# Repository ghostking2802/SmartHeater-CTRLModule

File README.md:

# Smart Heater Control Module 🔥

This project is a smart safety and control module for electric heaters. Designed using KiCad, it includes temperature monitoring, relay-based control, safety cutoffs, and visual feedback, all powered by a microcontroller (e.g., ESP32 or Arduino).

---

## 🧩 Features

- **Real-Time Temperature Monitoring**
- **Relay Control for Heater Switch**
- **Safety Cut-off with Thermal Fuse**
- **OLED Display for Status Info**
- **Manual Override Switch**
- **PCB Designed using KiCad**

---

## 📐 Block Diagram

---

## 🧪 Schematic

---

## 🛠️ PCB Layout Previews

---

## 📋 Bill of Materials (BOM)

| Component             | Qty | Cost     |
|-----------------------|-----|----------|
| ESP32 Dev Board       | 1   | Rs. 300  |
| DS18B20 Temp Sensor   | 1   | Rs. 100  |
| 5V Relay Module       | 1   | Rs. 60   |
| OLED Display (0.96")  | 1   | Rs. 150  |
| 7805 Regulator        | 1   | Rs. 15   |
| Discrete Components   | -   | Rs. 50   |
| PCB Fabrication       | 1   | Rs. 200  |

---

## 🔌 System Explanation

### Power Flow
AC Mains → Step-down SMPS → 5V/12V Regulated Supply → Microcontroller → Relay Control

### Sensor and Relay Logic
- If temperature < threshold → Relay ON → Heater ON  
- If temperature ≥ threshold → Relay OFF → Heater OFF  

### Safety & Fallback
- Thermal fuse as a hardware cutoff  
- Watchdog timer in software  
- Manual override and warning LED/OLED  

---

## 🧪 Test Plan

1. Simulate gradual temperature increase
2. Observe cutoff at 60°C
3. Check relay OFF and OLED warning
4. Allow manual reset below 50°C

---

## 📁 Project Structure

```
├── SmartHeaterControl.kicad_sch
├── SmartHeaterControl.kicad_pcb
├── gerber/
├── screenshots/
├── BlockDiagram.png
├── Schematic.png
└── PCB_View_*.png
```

---
## 💻 MCU Programming Guide

### Hardware Pin Mapping (ESP32)

| Component             | MCU Pin          |
|----------------------|------------------|
| DS18B20 Temp Sensor  | GPIO 4           |
| Relay Module (IN)    | GPIO 13          |
| OLED Display (I2C)   | SDA = GPIO 21, SCL = GPIO 22 |
| Buzzer / LED         | GPIO 14          |
| Manual Reset Button  | GPIO 12          |

> Note: DS18B20 needs a 4.7kΩ pull-up resistor on the data line.

---

### Required Libraries (Arduino IDE)

- `OneWire.h`
- `DallasTemperature.h`
- `Adafruit_GFX.h`
- `Adafruit_SSD1306.h`

---

### ESP32 Board Setup in Arduino IDE

1. Install board support:
   - Board Manager URL:  
     `https://raw.githubusercontent.com/espressif/arduino-esp32/gh-pages/package_esp32_index.json`
2. Select board: **ESP32 Dev Module**
3. Connect device via USB and select correct COM port
4. Install required libraries via Library Manager

---

## 👨‍💻 Author

**Soumabha Majumdar**  
📧 [soumabha.majumdar@gmail.com](mailto:soumabha.majumdar@gmail.com)  
📞 7003472159

---

## 📜 License

This project is open-source and free to use for academic and non-commercial purposes.

### 🔌 Sample Arduino Code

```cpp
#include <OneWire.h>
#include <DallasTemperature.h>
#include <Adafruit_GFX.h>
#include <Adafruit_SSD1306.h>

#define ONE_WIRE_BUS 4
#define RELAY_PIN 13
#define BUZZER_PIN 14
#define BUTTON_PIN 12

#define SCREEN_WIDTH 128
#define SCREEN_HEIGHT 64
Adafruit_SSD1306 display(SCREEN_WIDTH, SCREEN_HEIGHT, &Wire, -1);

OneWire oneWire(ONE_WIRE_BUS);
DallasTemperature sensors(&oneWire);

float cutoffTemp = 60.0;
float resumeTemp = 50.0;
bool manualReset = false;

void setup() {
  Serial.begin(115200);
  sensors.begin();

  pinMode(RELAY_PIN, OUTPUT);
  pinMode(BUZZER_PIN, OUTPUT);
  pinMode(BUTTON_PIN, INPUT_PULLUP);

  display.begin(SSD1306_SWITCHCAPVCC, 0x3C);
  display.clearDisplay();
  display.setTextSize(1);
  display.setTextColor(SSD1306_WHITE);
}

void loop() {
  sensors.requestTemperatures();
  float tempC = sensors.getTempCByIndex(0);

  display.clearDisplay();
  display.setCursor(0,0);
  display.print("Temp: ");
  display.print(tempC);
  display.print(" C");

  if (!manualReset && tempC < cutoffTemp) {
    digitalWrite(RELAY_PIN, HIGH);
    digitalWrite(BUZZER_PIN, LOW);
    display.setCursor(0,20);
    display.print("Status: Heater ON");
  } else if (!manualReset && tempC >= cutoffTemp) {
    digitalWrite(RELAY_PIN, LOW);
    digitalWrite(BUZZER_PIN, HIGH);
    display.setCursor(0,20);
    display.print("OVERHEAT! Relay OFF");
    display.setCursor(0,30);
    display.print("Press button to reset");
    manualReset = true;
  }

  if (manualReset && digitalRead(BUTTON_PIN) == LOW && tempC <= resumeTemp) {
    manualReset = false;
    digitalWrite(BUZZER_PIN, LOW);
  }

  display.display();
  delay(1000);
}

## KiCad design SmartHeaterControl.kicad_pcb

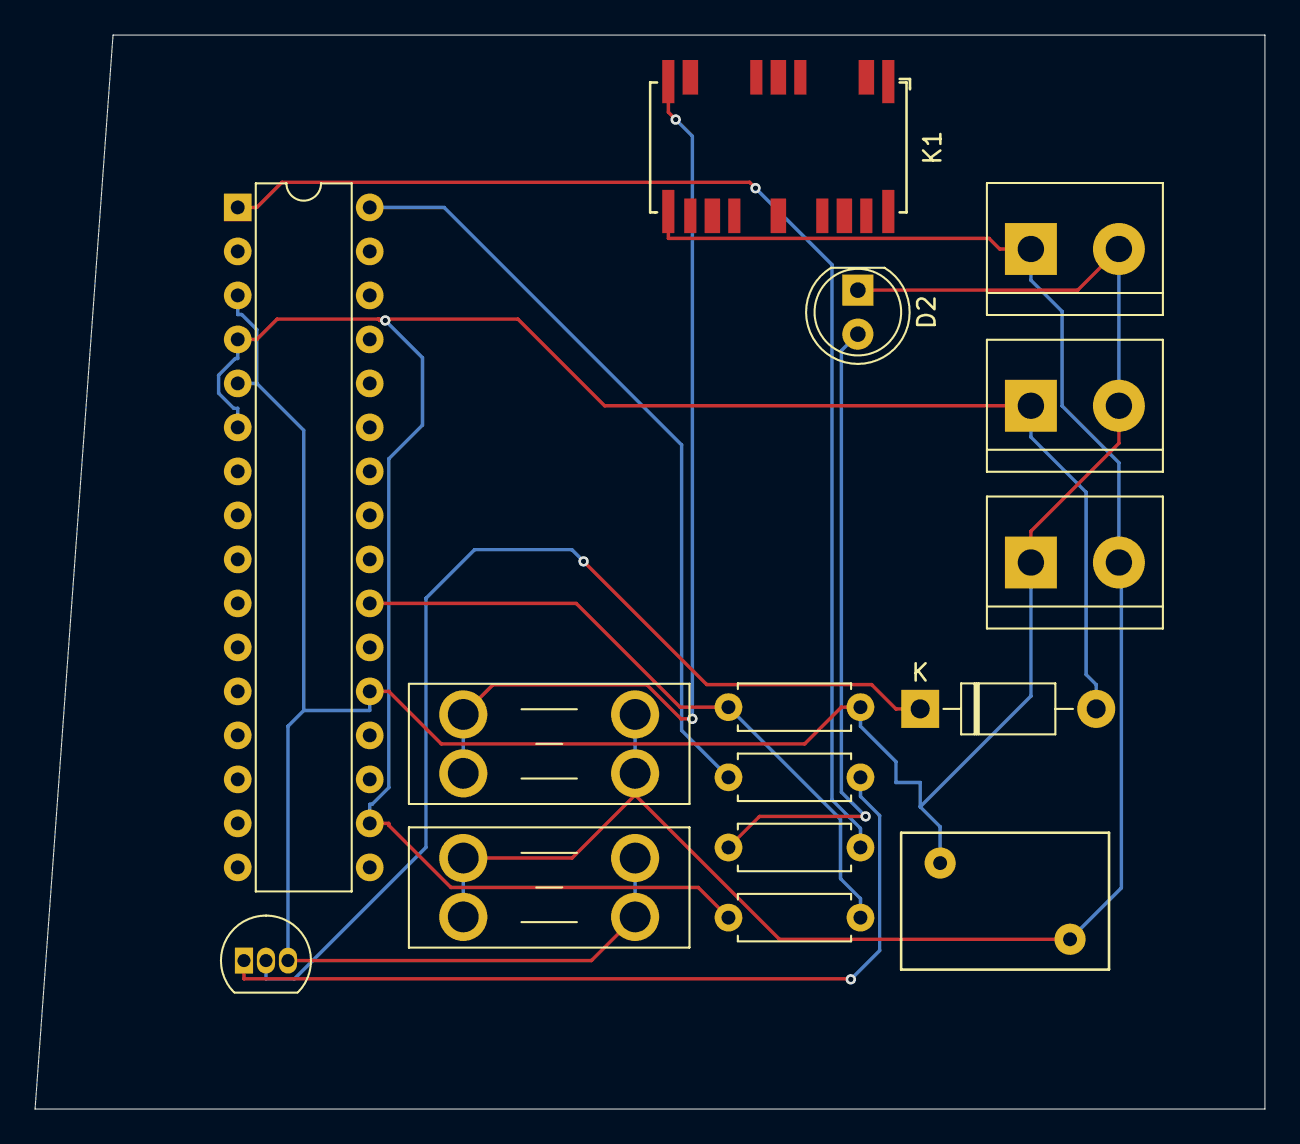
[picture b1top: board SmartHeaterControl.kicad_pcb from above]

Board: 2 copper layers, 71.0 x 62.0 mm, 15 parts (0 on the bottom side), 10 nets.

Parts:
D1: D; D_DO-41_SOD81_P10.16mm_Horizontal
D2: LED; LED_D5.0mm
F1, F2: Fuse; Fuseholder_Blade_Mini_Keystone_3568
J1, J2: Conn_01x02; TerminalBlock_bornier-2_P5.08mm
K1: Relay_SPDT; Relay_SPDT_AXICOM_HF3Series_50ohms_Pitch1.27mm
Q1: Q1; TO-92_Inline
R1, R2, R4: R; R_Axial_DIN0207_L6.3mm_D2.5mm_P7.62mm_Horizontal
R3: Heater; TerminalBlock_bornier-2_P5.08mm
RV1: Varistor; RV_Disc_D12mm_W7.9mm_P7.5mm
TH1: Thermistor_NTC; R_Axial_DIN0207_L6.3mm_D2.5mm_P7.62mm_Horizontal
U1: ATmega328P-A; DIP-32_W7.62mm

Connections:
+5V: D1.2 (A), J2.1, TH1.1, U1.4 (VCC), U1.6 (VCC), U1.18 (AVCC)
GND: D2.1 (K), F2.2, J1.2, J2.2, Q1.3 (E), R1.2, R3.1, RV1.1, U1.3 (GND), U1.5 (GND), U1.21 (GND)
unnamed: D1.1 (K), Q1.2 (C)
unnamed: D2.2 (A), R4.1
unnamed: F1.1, K1.11
unnamed: F1.2, F2.1, J1.1, K1.12, R3.2, RV1.2
unnamed: Q1.1 (B), R2.2
unnamed: R1.1, TH1.2, U1.23 (PC0)
unnamed: R2.1, U1.32 (PD2)
unnamed: R4.2, U1.1 (PD3)
